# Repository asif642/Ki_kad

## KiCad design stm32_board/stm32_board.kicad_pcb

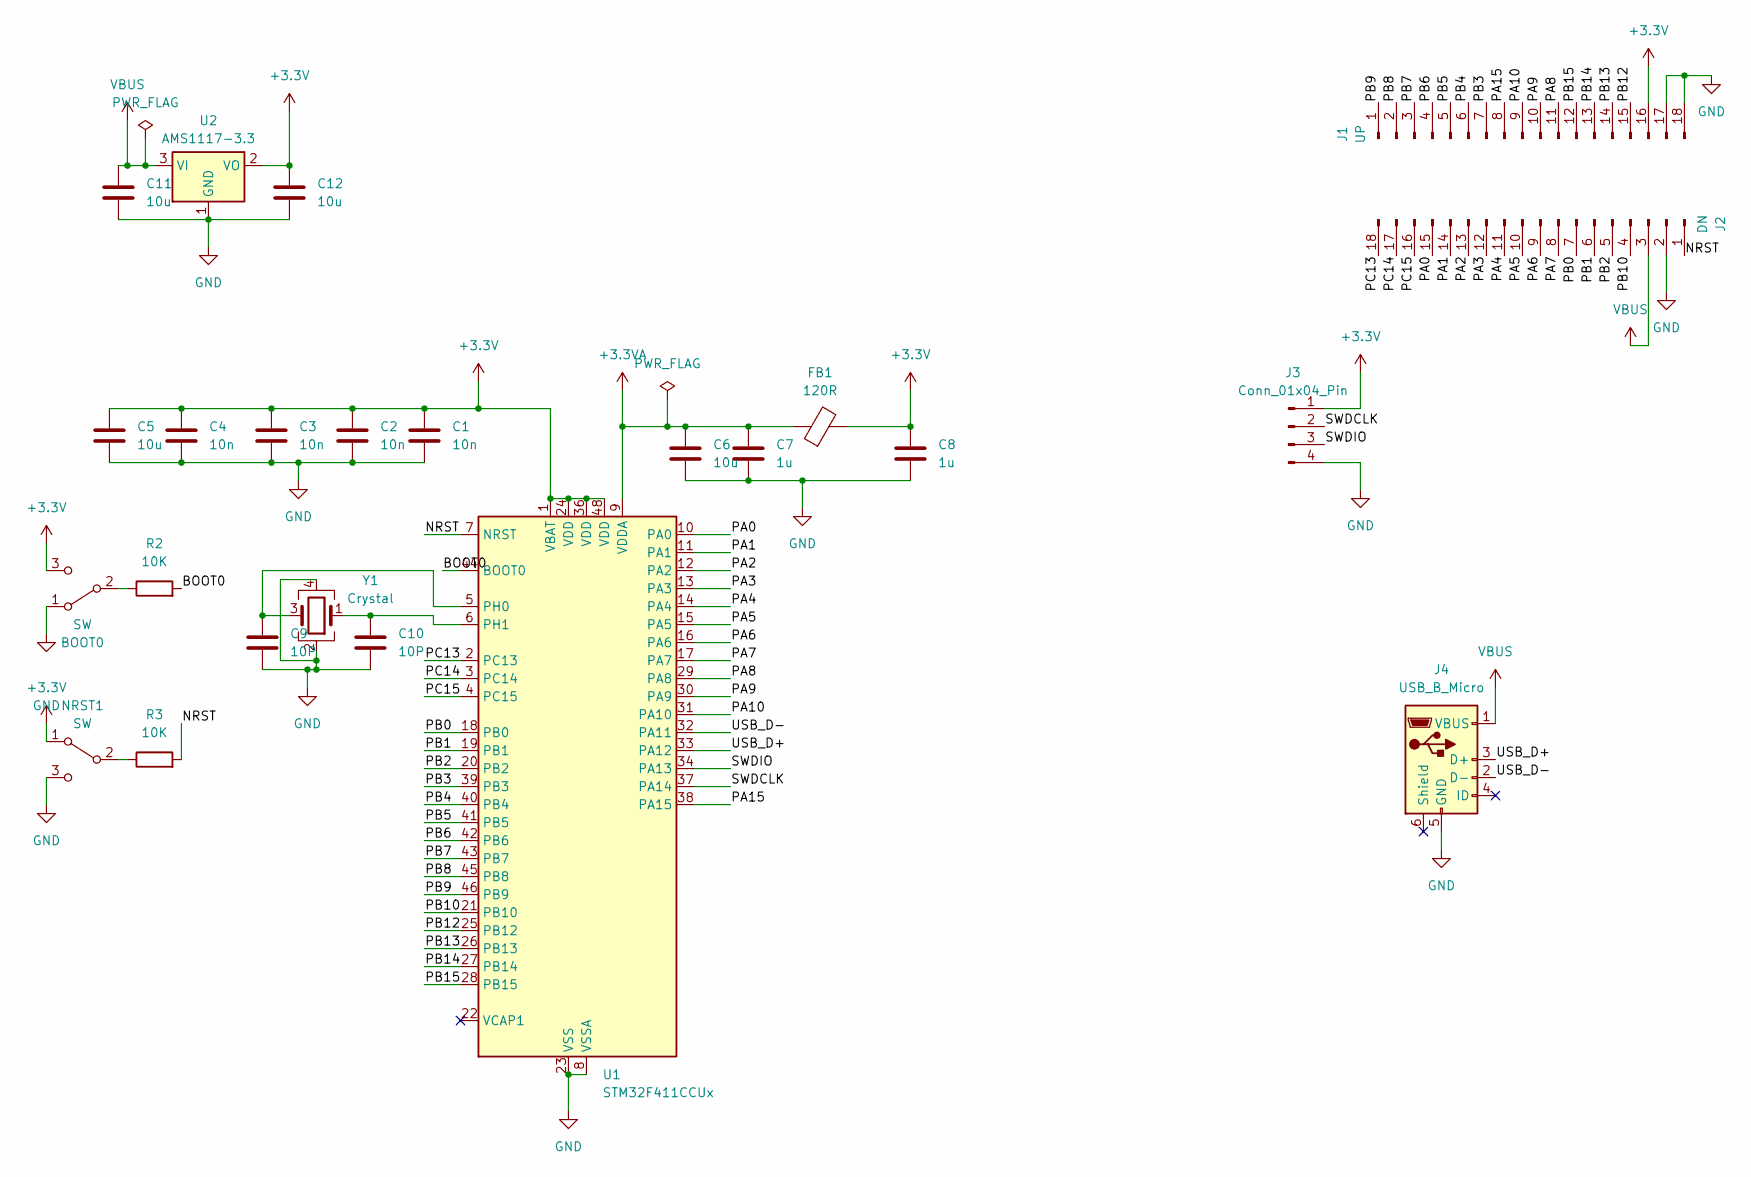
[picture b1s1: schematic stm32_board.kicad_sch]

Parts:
BOOT0: SW; SW_E-Switch_EG1271_SPDT
C1, C2, C3, C4: 10n; C_0402_1005Metric_Pad0.74x0.62mm_HandSolder
C5, C6, C11, C12: 10u; C_0402_1005Metric_Pad0.74x0.62mm_HandSolder
C7, C8: 1u; C_0402_1005Metric_Pad0.74x0.62mm_HandSolder
C9, C10: 10P; C_0402_1005Metric_Pad0.74x0.62mm_HandSolder
FB1: 120R; R_0402_1005Metric_Pad0.72x0.64mm_HandSolder
J1: UP; PinHeader_1x18_P2.54mm_Vertical
J2: DN; PinHeader_1x18_P2.54mm_Vertical
J3: Conn_01x04_Pin; PinHeader_1x04_P2.54mm_Vertical
J4: USB_B_Micro; USB_Micro-B_Amphenol_10103594-0001LF_Horizontal
NRST1: SW; SW_E-Switch_EG1271_SPDT
R2, R3: 10K; R_0402_1005Metric_Pad0.72x0.64mm_HandSolder
U1: STM32F411CCUx; QFN-48-1EP_7x7mm_P0.5mm_EP5.6x5.6mm
U2: AMS1117-3.3; SOT-223-3_TabPin2
Y1: Crystal; Crystal_SMD_0603-4Pin_6.0x3.5mm_HandSoldering

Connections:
+3.3V: BOOT0.3 (C), C1.1, C2.1, C3.1, C4.1, C5.1, C8.1, C12.1, FB1.2, J1.16, J3.1, NRST1.1 (A), U1.1 (VBAT), U1.24 (VDD), U1.36 (VDD), U1.48 (VDD), U2.2 (VO)
+3.3VA: C6.1, C7.1, FB1.1, U1.9 (VDDA)
/BOOT0: R2.2, U1.44 (BOOT0)
/NRST: J2.1, R3.2, U1.7 (NRST)
/PA0: J2.15, U1.10 (PA0)
/PA1: J2.14, U1.11 (PA1)
/PA2: J2.13, U1.12 (PA2)
/PA3: J2.12, U1.13 (PA3)
/PA4: J2.11, U1.14 (PA4)
/PA5: J2.10, U1.15 (PA5)
/PA6: J2.9, U1.16 (PA6)
/PA7: J2.8, U1.17 (PA7)
/PA8: J1.11, U1.29 (PA8)
/PA9: J1.10, U1.30 (PA9)
/PA10: J1.9, U1.31 (PA10)
/PA15: J1.8, U1.38 (PA15)
/PB0: J2.7, U1.18 (PB0)
/PB1: J2.6, U1.19 (PB1)
/PB2: J2.5, U1.20 (PB2)
/PB3: J1.7, U1.39 (PB3)
/PB4: J1.6, U1.40 (PB4)
/PB5: J1.5, U1.41 (PB5)
/PB6: J1.4, U1.42 (PB6)
/PB7: J1.3, U1.43 (PB7)
/PB8: J1.2, U1.45 (PB8)
/PB9: J1.1, U1.46 (PB9)
/PB10: J2.4, U1.21 (PB10)
/PB12: J1.15, U1.25 (PB12)
/PB13: J1.14, U1.26 (PB13)
/PB14: J1.13, U1.27 (PB14)
/PB15: J1.12, U1.28 (PB15)
/PC13: J2.18, U1.2 (PC13)
/PC14: J2.17, U1.3 (PC14)
/PC15: J2.16, U1.4 (PC15)
/SWDCLK: J3.2, U1.37 (PA14)
/SWDIO: J3.3, U1.34 (PA13)
/USB_D+: J4.3 (D+), U1.33 (PA12)
/USB_D-: J4.2 (D-), U1.32 (PA11)
GND: BOOT0.1 (A), C1.2, C2.2, C3.2, C4.2, C5.2, C6.2, C7.2, C8.2, C9.2, C10.2, C11.2, C12.2, J1.17, J1.18, J2.2, J3.4, J4.5 (GND), NRST1.3 (C), U1.8 (VSSA), U1.23 (VSS), U1.35 (VSS), U1.47 (VSS), U1.49 (VSS), U2.1 (GND), Y1.2, Y1.4
unnamed: BOOT0.2 (B), R2.1
unnamed: NRST1.2 (B), R3.1
unnamed: C9.1, U1.5 (PH0), Y1.3
unnamed: C10.1, U1.6 (PH1), Y1.1
VBUS: C11.1, J2.3, J4.1 (VBUS), U2.3 (VI)

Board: 2 copper layers, 24 parts (0 on the bottom side), 44 nets, no tracks yet.

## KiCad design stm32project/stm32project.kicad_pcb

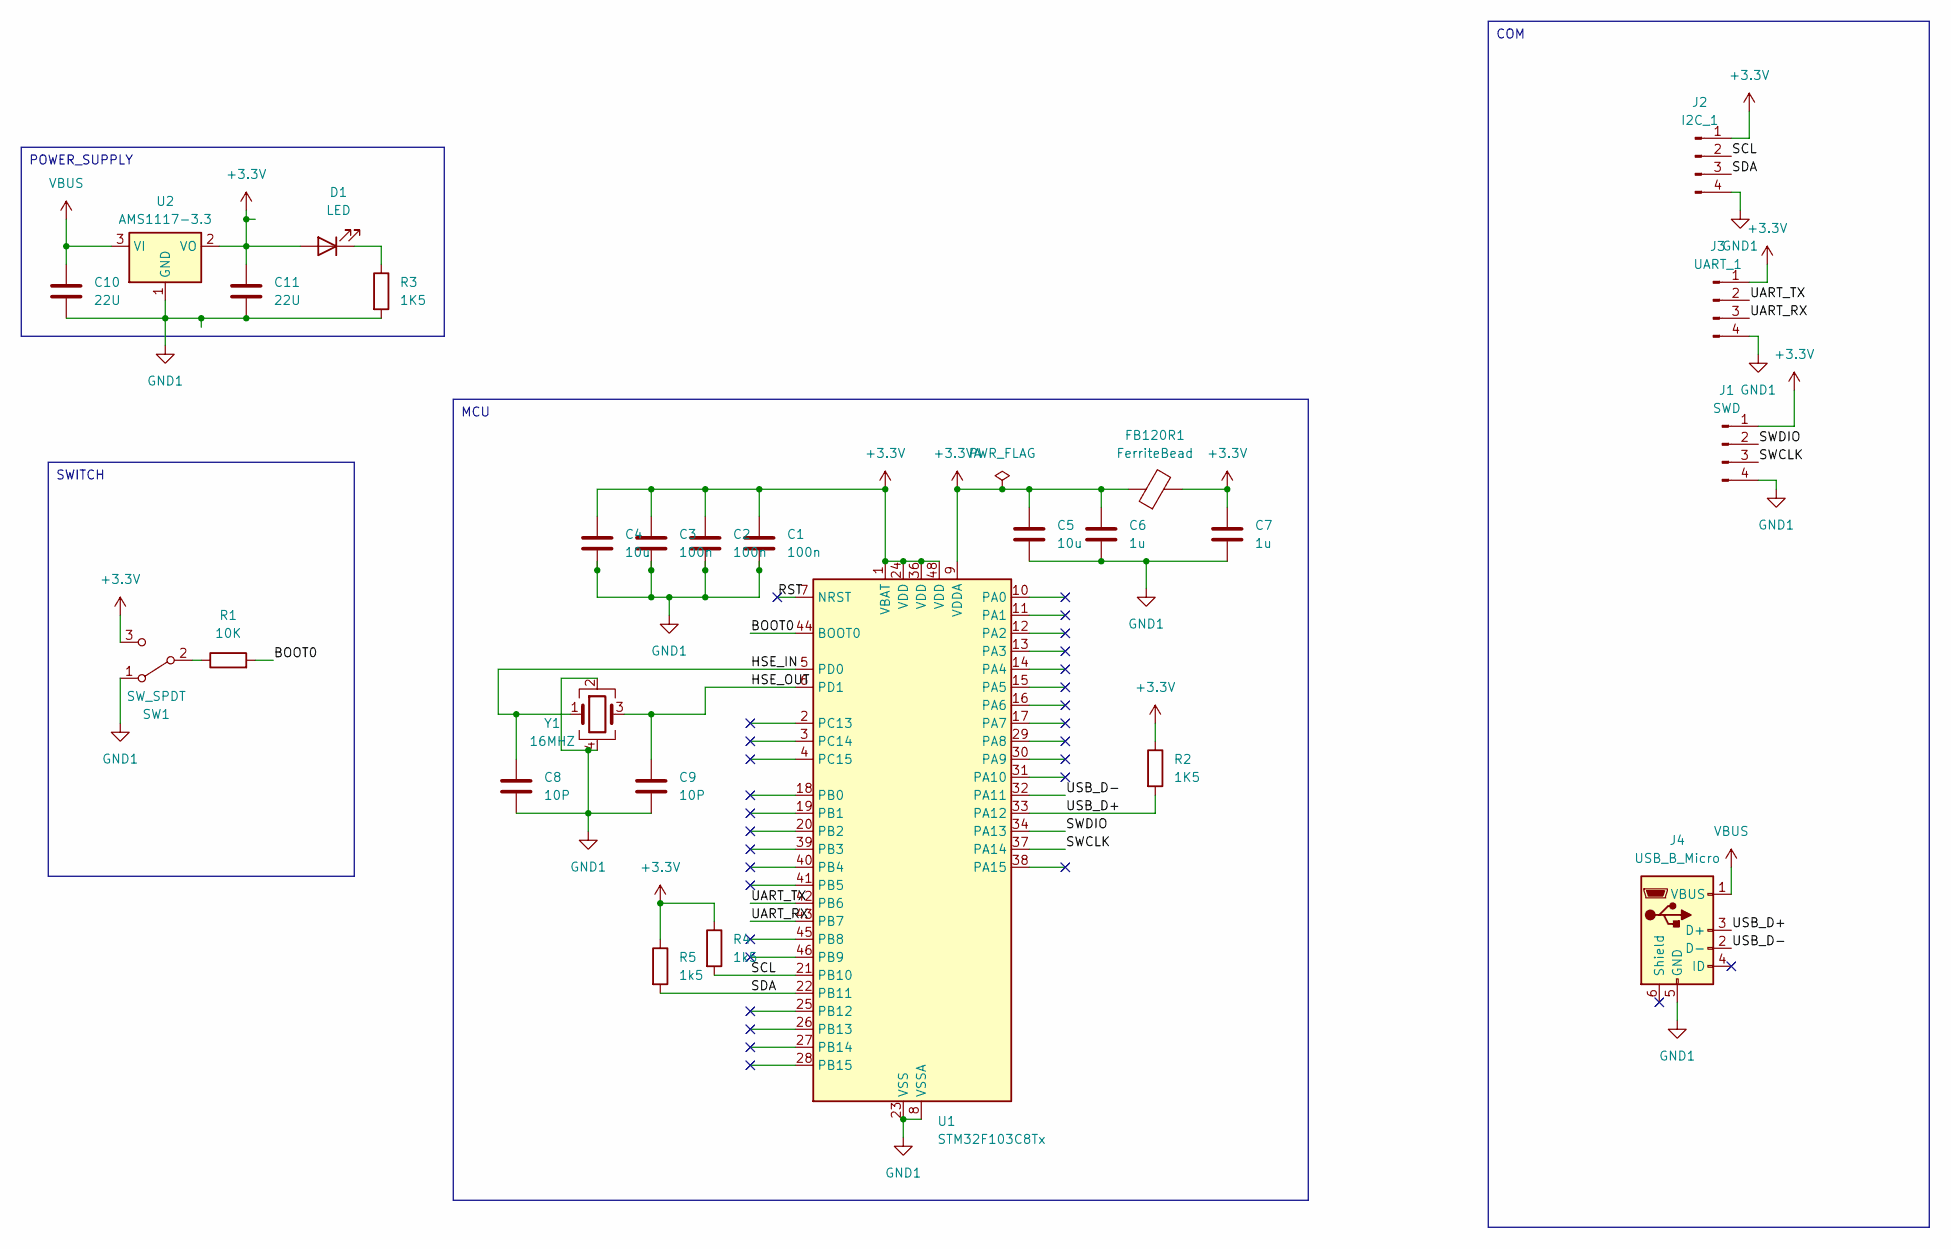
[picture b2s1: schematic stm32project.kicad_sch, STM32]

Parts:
C1, C2, C3: 100n; C_0402_1005Metric
C4, C5: 10u; C_0603_1608Metric
C6, C7: 1u; C_0402_1005Metric
C8, C9: 10P; C_0402_1005Metric
C10, C11: 22U; C_0805_2012Metric
D1: LED; LED_0805_2012Metric
FB120R1: FerriteBead; L_0603_1608Metric
J1: SWD; PinHeader_1x04_P2.54mm_Vertical
J2: I2C_1; PinHeader_1x04_P2.54mm_Vertical
J3: UART_1; PinHeader_1x04_P2.54mm_Vertical
J4: USB_B_Micro; USB_Micro-B_Amphenol_10103594-0001LF_Horizontal
R1: 10K; R_0603_1608Metric
R2, R3: 1K5; R_0603_1608Metric
R4, R5: 1k5; R_0805_2012Metric
SW1: SW_SPDT; Nidec_Copal_CAS-120A
U1: STM32F103C8Tx; LQFP-48_7x7mm_P0.5mm
U2: AMS1117-3.3; SOT-223-3_TabPin2
Y1: 16MHZ; Crystal_SMD_3225-4Pin_3.2x2.5mm_HandSoldering

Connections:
+3.3V: C1.1, C2.1, C3.1, C4.1, C7.1, C11.1, D1.2 (A), FB120R1.2, J1.1, J2.1, J3.1, R2.1, R4.1, R5.1, SW1.3 (C), U1.1 (VBAT), U1.24 (VDD), U1.36 (VDD), U1.48 (VDD), U2.2 (VO)
+3.3VA: C5.1, C6.1, FB120R1.1, U1.9 (VDDA)
/BOOT0: R1.2, U1.44 (BOOT0)
/HSE_IN: C8.1, U1.5 (PD0), Y1.1
/HSE_OUT: C9.1, U1.6 (PD1), Y1.3
/RST: U1.7 (NRST)
/SCL: J2.2, R4.2, U1.21 (PB10)
/SDA: J2.3, R5.2, U1.22 (PB11)
/SWCLK: J1.3, U1.37 (PA14)
/SWDIO: J1.2, U1.34 (PA13)
/UART_RX: J3.3, U1.43 (PB7)
/UART_TX: J3.2, U1.42 (PB6)
/USB_D+: J4.3 (D+), R2.2, U1.33 (PA12)
/USB_D-: J4.2 (D-), U1.32 (PA11)
GND1: C1.2, C2.2, C3.2, C4.2, C5.2, C6.2, C7.2, C8.2, C9.2, C10.2, C11.2, J1.4, J2.4, J3.4, J4.5 (GND), R3.2, SW1.1 (A), U1.8 (VSSA), U1.23 (VSS), U1.35 (VSS), U1.47 (VSS), U2.1 (GND), Y1.2, Y1.4
unnamed: D1.1 (K), R3.1
unnamed: R1.1, SW1.2 (B)
VBUS: C10.1, J4.1 (VBUS), U2.3 (VI)

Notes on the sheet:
COM
SWITCH
MCU
POWER_SUPPLY

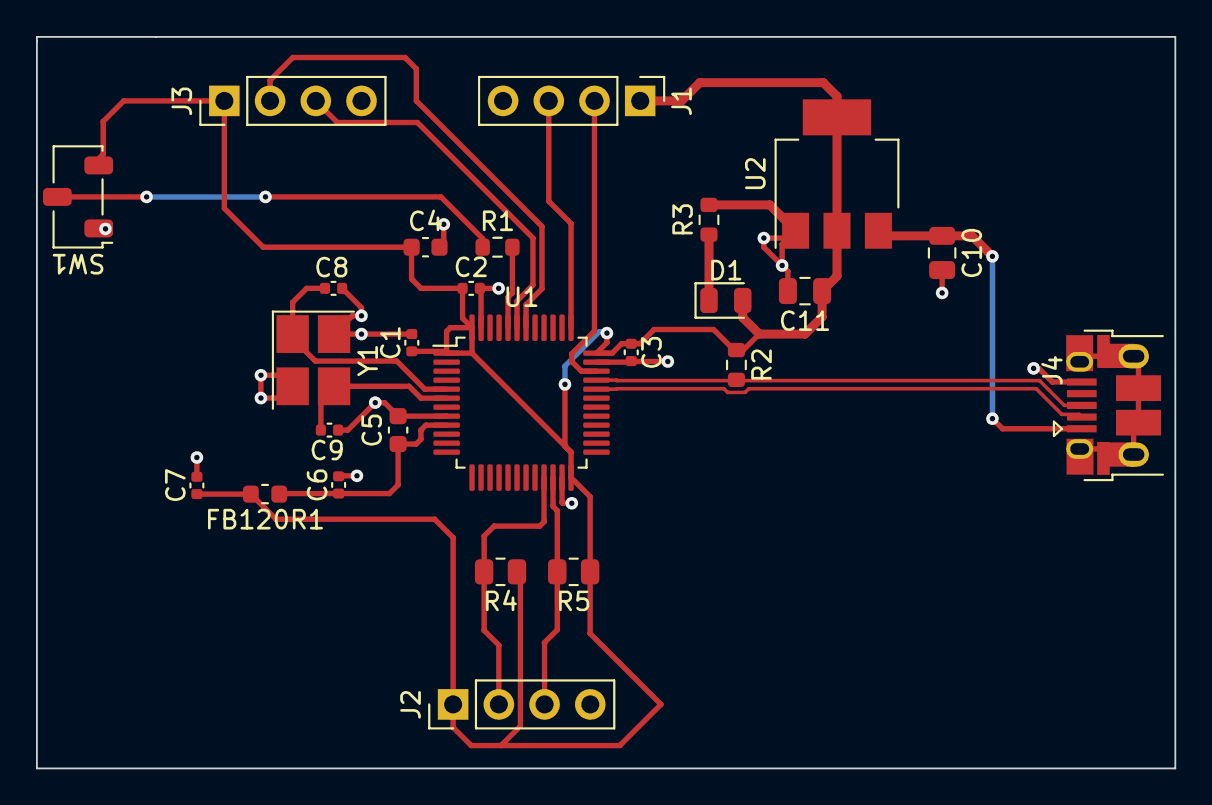
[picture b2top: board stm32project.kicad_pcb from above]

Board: 2 copper layers, 63.2 x 40.6 mm, 26 parts (0 on the bottom side), 17 nets.
